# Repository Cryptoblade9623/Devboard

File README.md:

# Devboard
A custom devboard using an RP2040

I used Kai Periera's starter project tutorial on stasis to make this RP2040 devboard.
I made it because I wanted to develop my skills and make more stuff. I also want to get more soldering practice.

This is the 3d case that I designed to hold and protect it. It has the word "Cryptoblade"- my gamer tag -etched on to the top.
It openes and closes using a sliding lid and is held in place with cylindrical 5x5x3mm neodynium magnets.

Once I get the parts I will:
1. Solder everything together
2. Glue the magnets into the case.
Then I'm done!

BOM

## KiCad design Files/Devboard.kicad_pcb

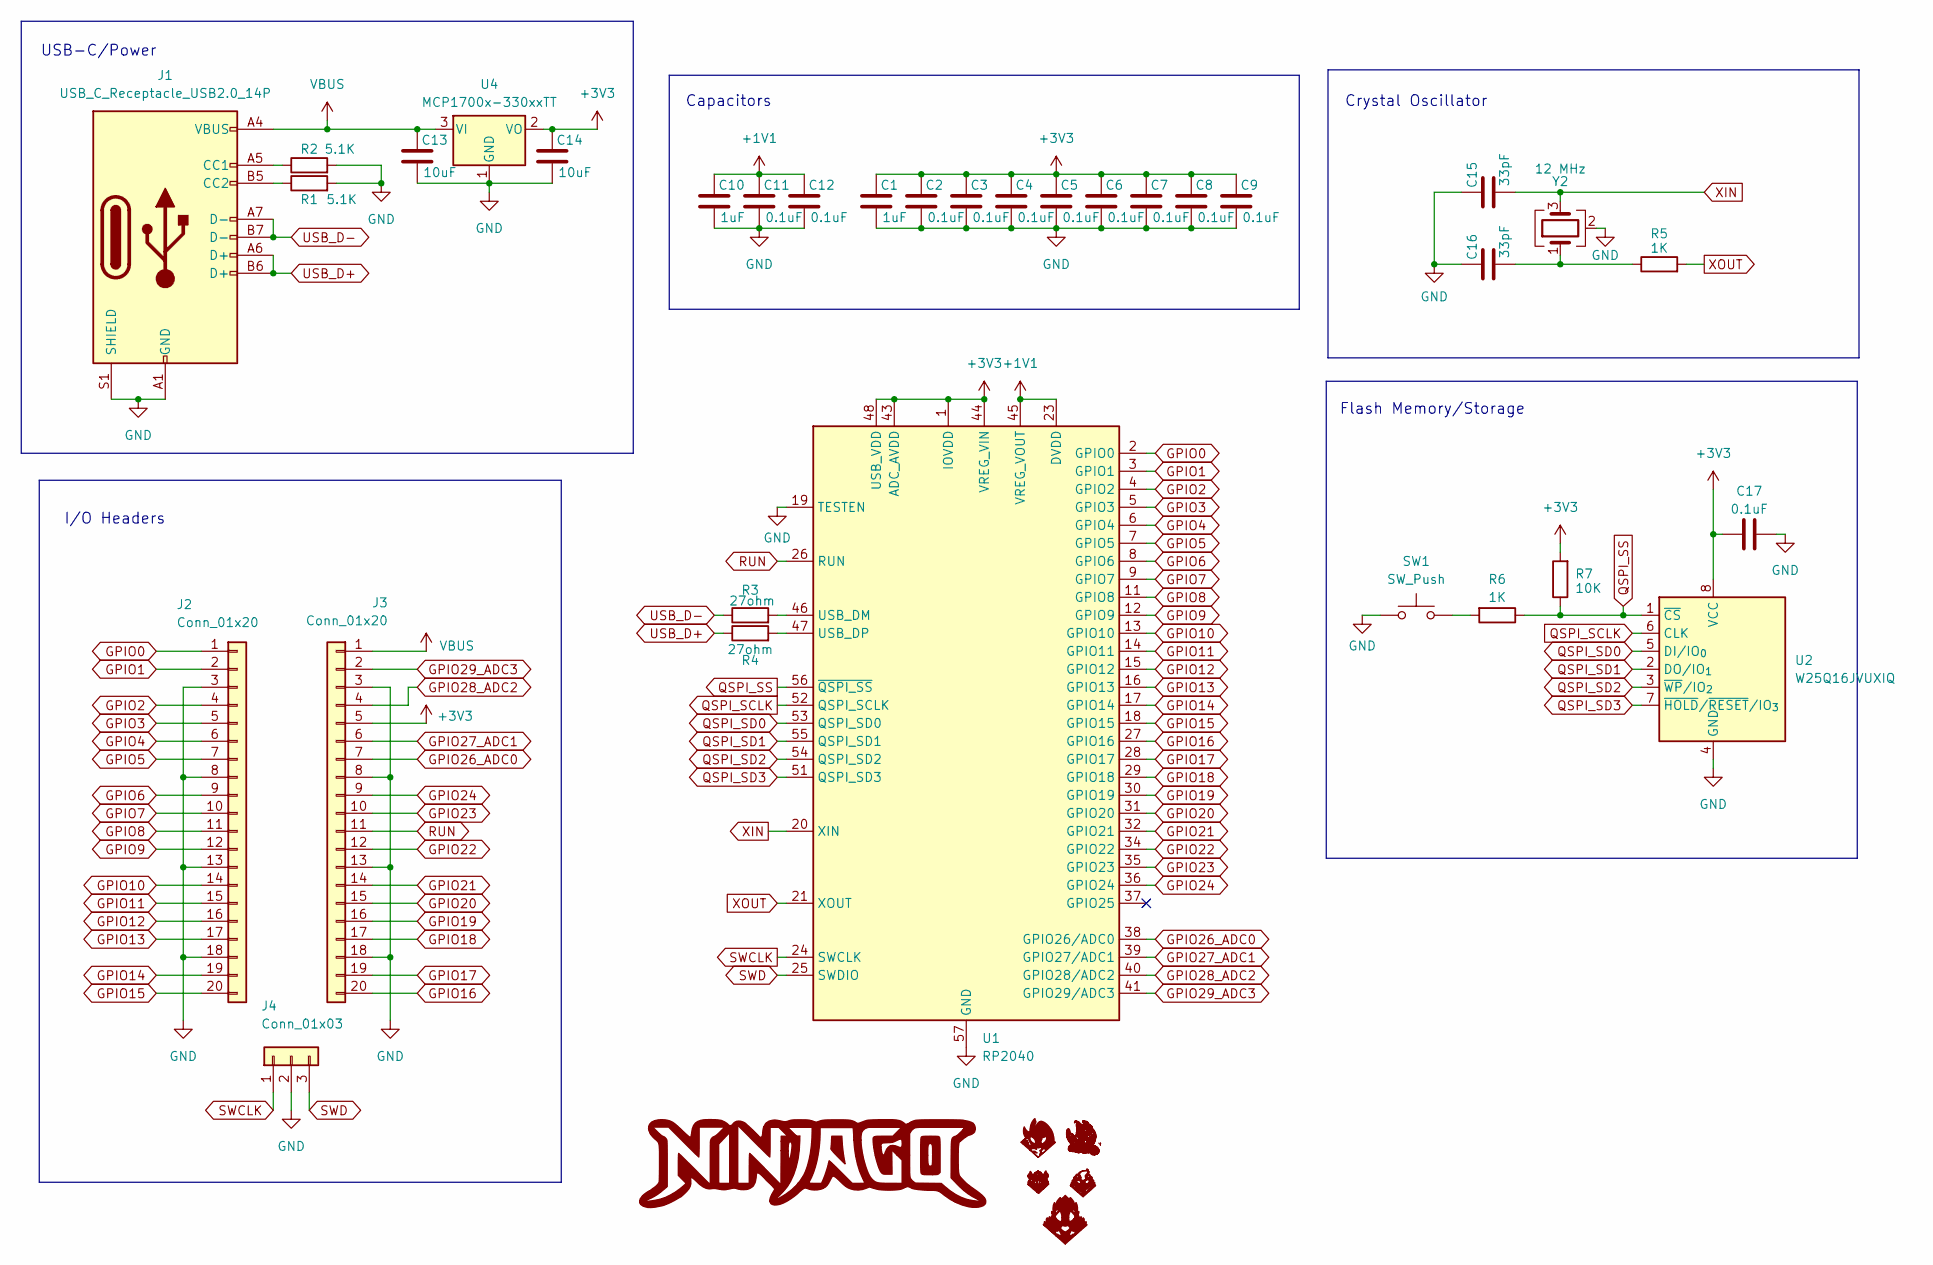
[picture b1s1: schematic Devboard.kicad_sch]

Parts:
C1, C10: 1uF; C_0402_1005Metric
C2, C3, C4, C5, C6, C7, C8, C9, C11, C12, C17: 0.1uF; C_0402_1005Metric
C13, C14: 10uF; C_0603_1608Metric
C15, C16: 33pF; C_0402_1005Metric
J1: USB_C_Receptacle_USB2.0_14P; USB_C_Receptacle_HRO_TYPE-C-31-M-12
J2, J3: Conn_01x20; PinHeader_1x20_P2.54mm_Vertical
J4: Conn_01x03; PinHeader_1x03_P2.54mm_Vertical
LOGO1: LOGO; ninjago
LOGO3: LOGO; igris3
LOGO4: LOGO; iron3
LOGO5: LOGO; tank3
LOGO6: LOGO; kaisel
LOGO7: LOGO; beru
R1, R2: 5.1K; R_0402_1005Metric
R3, R4: 27ohm; R_0402_1005Metric
R5, R6: 1K; R_0402_1005Metric
R7: 10K; R_0402_1005Metric
SW1: SW_Push; SW_Push_SPST_NO_Alps_SKRK
U1: RP2040; QFN-56-1EP_7x7mm_P0.4mm_EP3.2x3.2mm
U2: W25Q16JVUXIQ; Winbond_USON-8-1EP_3x2mm_P0.5mm_EP0.2x1.6mm
U4: MCP1700x-330xxTT; SOT-23
Y2: 12 MHz; Crystal_SMD_3225-4Pin_3.2x2.5mm

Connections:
+1V1: C10.1, C11.1, C12.1, U1.23 (DVDD), U1.45 (VREG_VOUT), U1.50 (DVDD)
+3V3: C1.1, C2.1, C3.1, C4.1, C5.1, C6.1, C7.1, C8.1, C9.1, C14.1, C17.1, J3.5, R7.2, U1.1 (IOVDD), U1.10 (IOVDD), U1.22 (IOVDD), U1.33 (IOVDD), U1.42 (IOVDD), U1.43 (ADC_AVDD), U1.44 (VREG_VIN), U1.48 (USB_VDD), U1.49 (IOVDD), U2.8 (VCC), U4.2 (VO)
GND: C1.2, C2.2, C3.2, C4.2, C5.2, C6.2, C7.2, C8.2, C9.2, C10.2, C11.2, C12.2, C13.2, C14.2, C15.1, C16.1, C17.2, J1.A1 (GND), J1.A12 (GND), J1.B1 (GND), J1.B12 (GND), J1.S1 (SHIELD), J2.3, J2.8, J2.13, J2.18, J3.3, J3.8, J3.13, J3.18, J4.2, R1.2, R2.2, SW1.1, U1.19 (TESTEN), U1.57 (GND), U2.4 (GND), U4.1 (GND), Y2.2 (G), Y2.4 (G)
GPIO0: J2.1, U1.2 (GPIO0)
GPIO1: J2.2, U1.3 (GPIO1)
GPIO2: J2.4, U1.4 (GPIO2)
GPIO3: J2.5, U1.5 (GPIO3)
GPIO4: J2.6, U1.6 (GPIO4)
GPIO5: J2.7, U1.7 (GPIO5)
GPIO6: J2.9, U1.8 (GPIO6)
GPIO7: J2.10, U1.9 (GPIO7)
GPIO8: J2.11, U1.11 (GPIO8)
GPIO9: J2.12, U1.12 (GPIO9)
GPIO10: J2.14, U1.13 (GPIO10)
GPIO11: J2.15, U1.14 (GPIO11)
GPIO12: J2.16, U1.15 (GPIO12)
GPIO13: J2.17, U1.16 (GPIO13)
GPIO14: J2.19, U1.17 (GPIO14)
GPIO15: J2.20, U1.18 (GPIO15)
GPIO16: J3.20, U1.27 (GPIO16)
GPIO17: J3.19, U1.28 (GPIO17)
GPIO18: J3.17, U1.29 (GPIO18)
GPIO19: J3.16, U1.30 (GPIO19)
GPIO20: J3.15, U1.31 (GPIO20)
GPIO21: J3.14, U1.32 (GPIO21)
GPIO22: J3.12, U1.34 (GPIO22)
GPIO23: J3.10, U1.35 (GPIO23)
GPIO24: J3.9, U1.36 (GPIO24)
GPIO26_ADC0: J3.7, U1.38 (GPIO26/ADC0)
GPIO27_ADC1: J3.6, U1.39 (GPIO27/ADC1)
GPIO28_ADC2: J3.4, U1.40 (GPIO28/ADC2)
GPIO29_ADC3: J3.2, U1.41 (GPIO29/ADC3)
unnamed: C16.2, R5.1, Y2.1
unnamed: J1.A5 (CC1), R2.1
unnamed: J1.B5 (CC2), R1.1
unnamed: R6.2, SW1.2
unnamed: R3.2, U1.46 (USB_DM)
unnamed: R4.2, U1.47 (USB_DP)
QSPI_SCLK: U1.52 (QSPI_SCLK), U2.6 (CLK)
QSPI_SD0: U1.53 (QSPI_SD0), U2.5 (DI/IO_{0})
QSPI_SD1: U1.55 (QSPI_SD1), U2.2 (DO/IO_{1})
QSPI_SD2: U1.54 (QSPI_SD2), U2.3 (~WP/IO_{2})
QSPI_SD3: U1.51 (QSPI_SD3), U2.7 (~HOLD/~RESET/IO_{3})
QSPI_SS: R6.1, R7.1, U1.56 (~QSPI_SS), U2.1 (~CS)
RUN: J3.11, U1.26 (RUN)
SWCLK: J4.1, U1.24 (SWCLK)
SWD: J4.3, U1.25 (SWDIO)
USB_D+: J1.A6 (D+), J1.B6 (D+), R4.1
USB_D-: J1.A7 (D-), J1.B7 (D-), R3.1
VBUS: C13.1, J1.A4 (VBUS), J1.A9 (VBUS), J1.B4 (VBUS), J1.B9 (VBUS), J3.1, U4.3 (VI)
XIN: C15.2, U1.20 (XIN), Y2.3
XOUT: R5.2, U1.21 (XOUT)

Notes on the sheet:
Crystal Oscillator
Flash Memory/Storage
Capacitors
USB-C/Power
I/O Headers

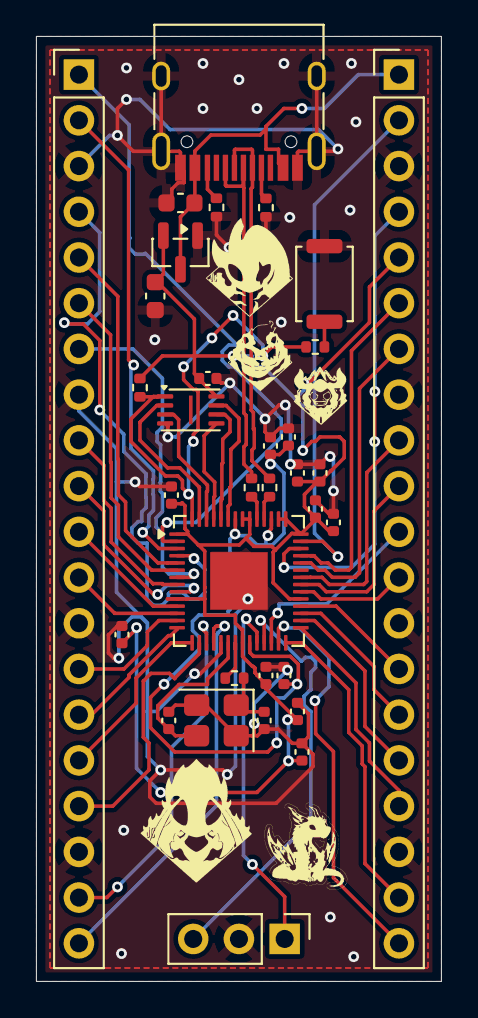
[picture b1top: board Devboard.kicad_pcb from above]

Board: 2 copper layers, 22.5 x 52.5 mm, 39 parts (1 on the bottom side), 52 nets.

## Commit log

2026-05-15 Update README with project details and images
    Added images and project details for the RP2040 devboard.
2026-05-17 Create KiCad Files
2026-05-17 Create 3D Files
2026-05-17 Create fudin
